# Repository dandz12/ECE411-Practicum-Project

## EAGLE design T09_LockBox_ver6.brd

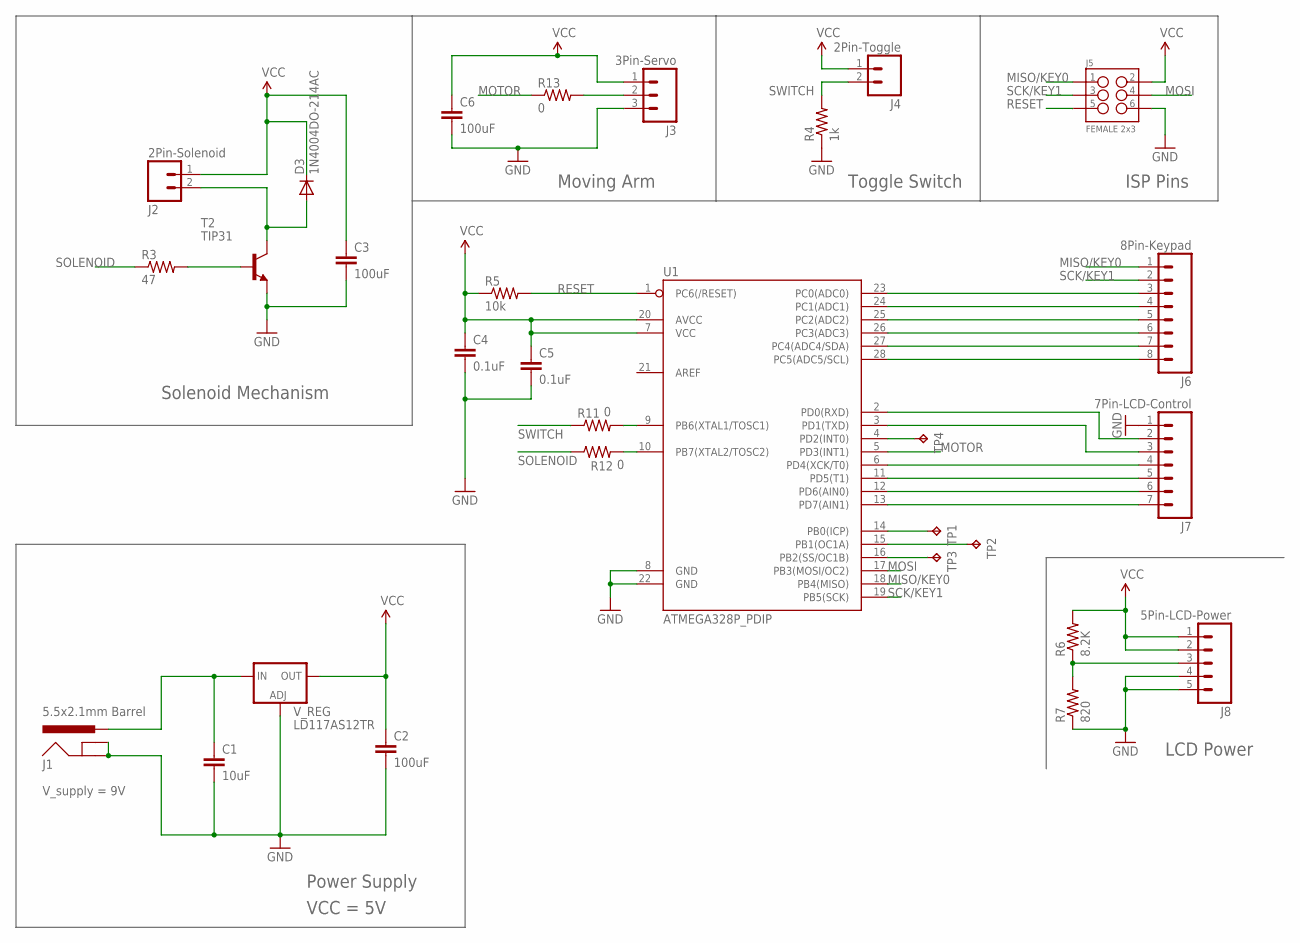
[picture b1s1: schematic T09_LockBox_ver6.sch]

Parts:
C1: 10uF; 0603-CAP
C2, C3, C6: 100uF; 0603-CAP
C4, C5: 0.1uF; 0603-CAP
D3: 1N4004DO-214AC; DO-214AC
J1: 5.5x2.1mm Barrel; POWER_JACK_SMD
J2: 2Pin-Solenoid; 1X02
J3: 3Pin-Servo; 1X03
J4: 2Pin-Toggle; 1X02
J5: FEMALE 2x3; 2X3
J6: 8Pin-Keypad; 1X08_ROUND
J7: 7Pin-LCD-Control; 1X07
J8: 5Pin-LCD-Power; 1X05
R3: 47; 0805
R4: 1k; 0603-RES
R5: 10k; 0603-RES
R6: 8.2K; 0603-RES
R7: 820; 0603-RES
R11, R12, R13: 0; 0603-RES
T2: TIP31; TO220
TP1, TP2, TP3, TP4: TPPAD1-13; P1-13
U1: ATMEGA328P_PDIP; DIL28-3
V_REG: LD117AS12TR; SOT223

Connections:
GND: C1.2, C2.2, C3.2, C4.2, C5.2, C6.2, J1.GND (GNDBREAK), J1.P$4 (GND), J3.3, J5.6, J7.1, J8.4, J8.5, R4.1, R7.1, T2.3 (E), U1.8 (GND), U1.22 (GND), V_REG.1 (ADJ)
MISO/KEY0: J5.1, J6.1, U1.18 (PB4(MISO))
MOSI: J5.4, U1.17 (PB3(MOSI/OC2))
MOTOR: R13.1, U1.5 (PD3(INT1))
unnamed: D3.A, J2.2, T2.2 (C)
unnamed: J8.3, R6.1, R7.2
unnamed: R3.2, T2.1 (B)
unnamed: J7.2, U1.2 (PD0(RXD))
unnamed: R11.2, U1.9 (PB6(XTAL1/TOSC1))
unnamed: R12.2, U1.10 (PB7(XTAL2/TOSC2))
unnamed: J3.2, R13.2
unnamed: J7.3, U1.3 (PD1(TXD))
unnamed: J7.4, U1.6 (PD4(XCK/T0))
unnamed: J7.5, U1.11 (PD5(T1))
unnamed: J7.6, U1.12 (PD6(AIN0))
unnamed: J7.7, U1.13 (PD7(AIN1))
unnamed: J6.3, U1.23 (PC0(ADC0))
unnamed: J6.4, U1.24 (PC1(ADC1))
unnamed: J6.5, U1.25 (PC2(ADC2))
unnamed: J6.6, U1.26 (PC3(ADC3))
unnamed: J6.7, U1.27 (PC4(ADC4/SDA))
unnamed: J6.8, U1.28 (PC5(ADC5/SCL))
unnamed: TP4.TP, U1.4 (PD2(INT0))
unnamed: TP1.TP, U1.14 (PB0(ICP))
unnamed: TP2.TP, U1.15 (PB1(OC1A))
unnamed: TP3.TP, U1.16 (PB2(SS/OC1B))
RESET: J5.5, R5.2, U1.1 (PC6(/RESET))
SCK/KEY1: J5.3, J6.2, U1.19 (PB5(SCK))
SOLENOID: R3.1, R12.1
SWITCH: J4.2, R4.2, R11.1
VCC: C2.1, C3.1, C4.1, C5.1, C6.1, D3.C, J2.1, J3.1, J4.1, J5.2, J8.1, J8.2, R5.1, R6.2, U1.7 (VCC), U1.20 (AVCC), V_REG.4 (OUT)
VIN: C1.1, J1.VIN0 (PWR), V_REG.3 (IN)

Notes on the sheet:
VCC = 5V
Solenoid Mechanism
Moving Arm
ISP Pins
Toggle Switch
Power Supply
LCD Power
V_supply = 9V

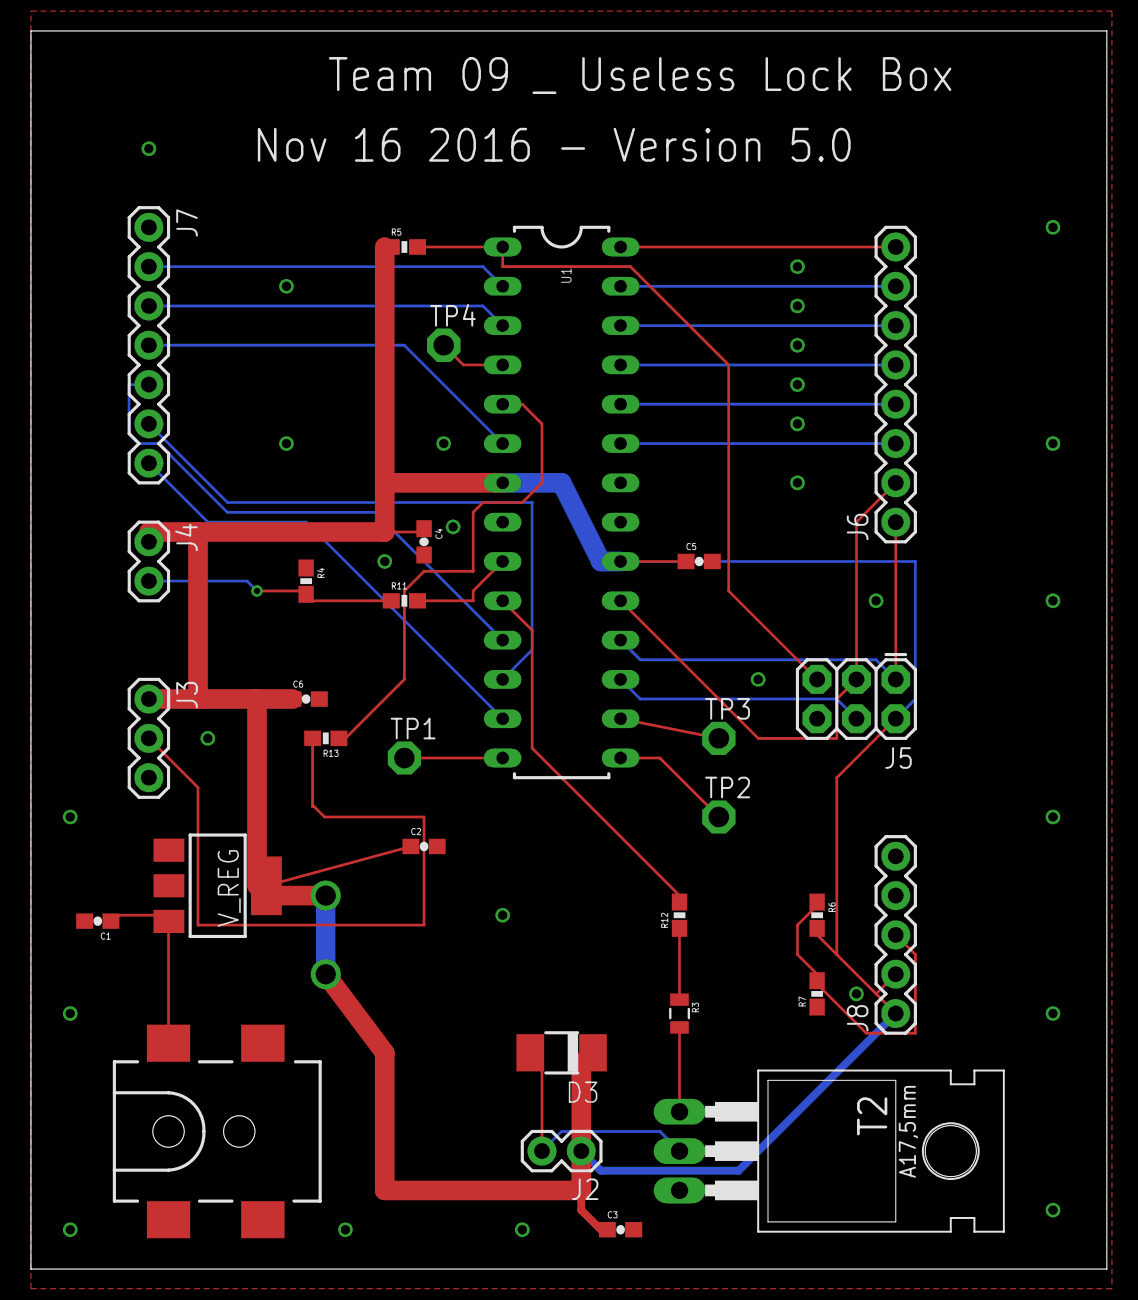
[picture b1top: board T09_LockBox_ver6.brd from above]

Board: 2 copper layers, 69.5 x 80.0 mm, 30 parts (0 on the bottom side), 32 nets.

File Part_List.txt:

Partlist exported from /Users/BumBum/Desktop/T09_LockBox_ver5.0.sch at 11/19/16 9:20 PM

Part  Value            Device           Package        Description			
C1    10uF             CAP0603-CAP      0603-CAP       Capacitor                                                                                                         
C2    100uF            CAP0603-CAP      0603-CAP       Capacitor                                                                                                         
C3    100uF            CAP0603-CAP      0603-CAP       Capacitor                                                                                                         
C4    0.1uF            CAP0603-CAP      0603-CAP       Capacitor                                                                                                         
C5    0.1uF            CAP0603-CAP      0603-CAP       Capacitor                                                                                                         
C6    100uF            CAP0603-CAP      0603-CAP       Capacitor                                                                                                         
D3    1N4004DO-214AC   1N4004DO-214AC   DO-214AC       DIODE                                                                                                             
J1    5.5x2.1mm Barrel POWER_JACKSMD    POWER_JACK_SMD Power Jack                                                 
J2    2Pin-Solenoid    M02PTH           1X02           Header 2                                                                             
J3    3Pin-Servo       M03PTH           1X03           Header 3                                                                                                          
J4    2Pin-Toggle      M02PTH           1X02           Header 2
J5    FEMALE 2x3       M03X2FEMALE      2X3            2x3 .1" header                                             
J6    8Pin-Keypad      M08              1X08_ROUND     Header 8                                                   
J7    7Pin-LCD-Control M07              1X07           Header 7                                                                                                          
J8    5Pin-LCD-Power   M05PTH           1X05           Header 5                                                                                                          
R3    47               RESISTOR0805-RES 0805           Resistor                                                                                                          
R4    1k               RESISTOR0603     0603-RES       Resistor                                                                                                          
R5    10k              RESISTOR0603     0603-RES       Resistor                                                                                                          
R6    8.2K             RESISTOR0603     0603-RES       Resistor                                                                                                          
R7    820              RESISTOR0603     0603-RES       Resistor                                                                                                          
R11   0                RESISTOR0603     0603-RES       Resistor                                                                                                          
R12   0                RESISTOR0603     0603-RES       Resistor                                                                                                          
R13   0                RESISTOR0603     0603-RES       Resistor                                                                                                          
T2    TIP31            TIP31            TO220          NPN Transistor                                                         
TP1   TPPAD1-13        TPPAD1-13        P1-13          Test pad                                                                                                          
TP2   TPPAD1-13        TPPAD1-13        P1-13          Test pad                                                                                                          
TP3   TPPAD1-13        TPPAD1-13        P1-13          Test pad                                                                                                          
TP4   TPPAD1-13        TPPAD1-13        P1-13 in       Test pad                                                                                                          
U1    ATMEGA328P_PDIP  ATMEGA328P_PDIP  DIL28-3        uC used in the Arduino                                                                                            
V_REG LD117AS12TR      LD117AS12TR      SOT223         Positive voltage regulators 1A

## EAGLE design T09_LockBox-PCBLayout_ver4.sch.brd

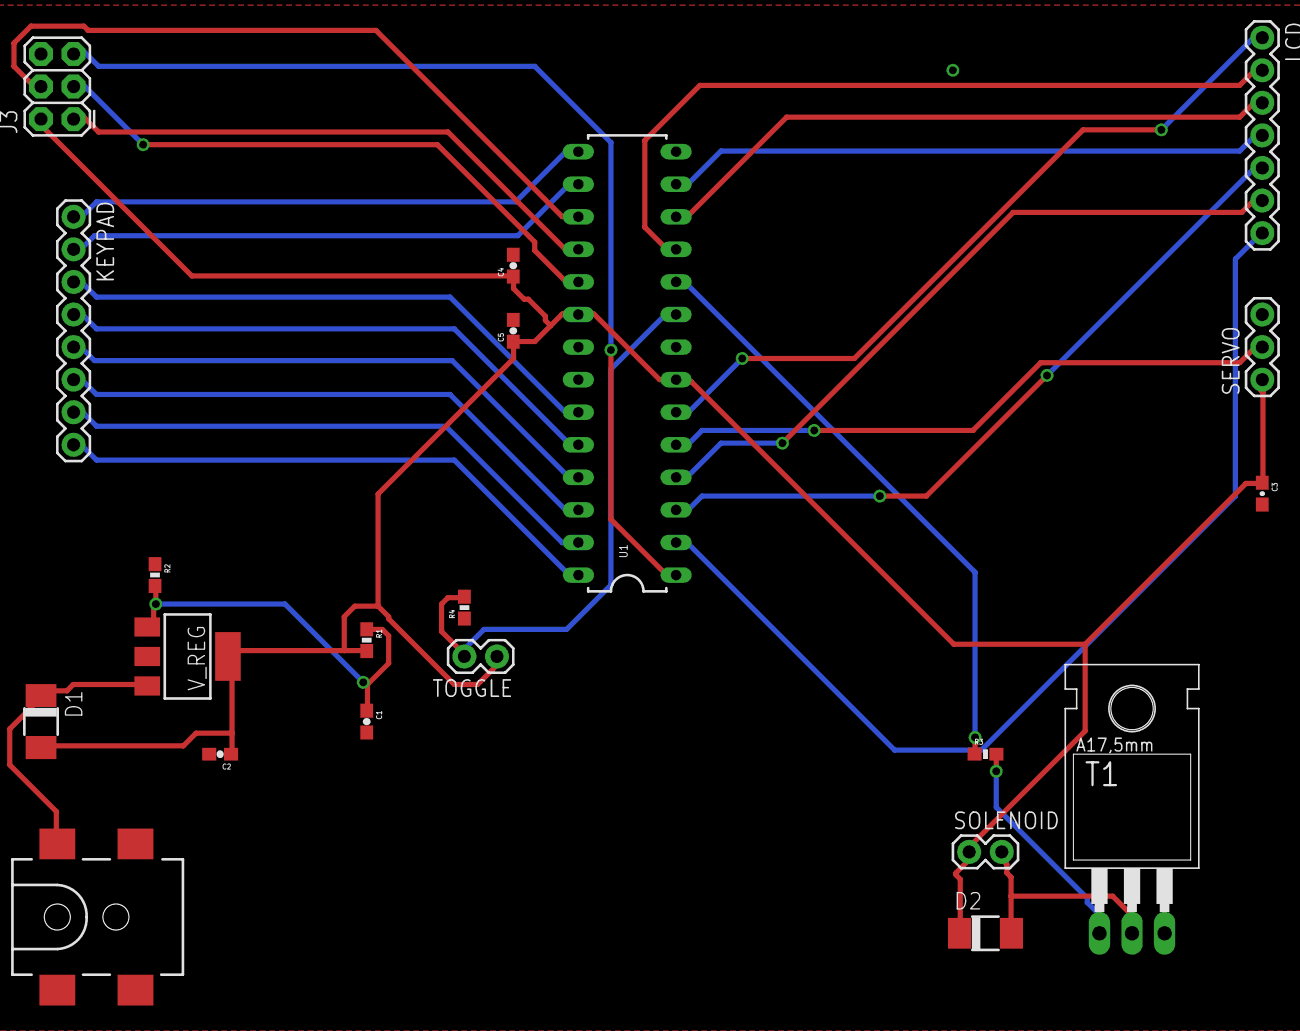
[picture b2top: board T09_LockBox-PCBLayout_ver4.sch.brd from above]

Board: 2 copper layers, 21 parts (0 on the bottom side), 28 nets.

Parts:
C1: 10uF; 0603-CAP
C2, C4, C5: 220uF; 0603-CAP
C3: 470uF; 0603-CAP
D1, D2: 1N4004DO-214AC; DO-214AC
J1: 5.5x2.1mm Barrel; POWER_JACK_SMD
J3: FEMALE 2x3; 2X3
KEYPAD: 8-Pins; 1X08_ROUND
LCD: 7-Pins; 1X07
R1: 120; 0603-RES
R2: 360; 0603-RES
R3: 2k2; 0603-RES
R4: 1k; 0603-RES
SERVO: 3-Pins; 1X03
SOLENOID: 2-Pins; 1X02
T1: TIP31; TO220
TOGGLE: 2-Pins; 1X02
U1: ATMEGA328P_PDIP; DIL28-3
V_REG: LD117AS12TR; SOT223

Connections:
DATA1: LCD.1, U1.6
DATA2: LCD.2, U1.11
DATA3: LCD.3, U1.12
DATA4: LCD.4, U1.13
EN: LCD.7, U1.2
GND: C1.2, C2.2, C3.2, C4.2, C5.2, J1.GND, J1.P$4, J3.6, R2.1, R4.1, SERVO.3, T1.3, U1.8, U1.22
KEY1: KEYPAD.1, U1.15
KEY2: KEYPAD.2, U1.16
KEY3: KEYPAD.3, U1.23
KEY4: KEYPAD.4, U1.24
KEY5: KEYPAD.5, U1.25
KEY6: KEYPAD.6, U1.26
KEY7: KEYPAD.7, U1.27
KEY8: KEYPAD.8, U1.28
MISO: J3.1, U1.18
MOSI: J3.4, U1.17
MOTOR: SERVO.2, U1.5
unnamed: R3.2, T1.1
unnamed: C1.1, R1.1, R2.2, V_REG.1
RESET: J3.5, U1.1
RS: LCD.6, U1.4
SCK: J3.3, U1.19
SOLENOID: R3.1, U1.10
SOLENOID-: D2.A, SOLENOID.2, T1.2
SWITCH: R4.2, TOGGLE.2, U1.9
VCC: C2.1, C3.1, C4.1, C5.1, D1.A, D2.C, J3.2, R1.2, SERVO.1, SOLENOID.1, TOGGLE.1, U1.7, U1.20, V_REG.4
VIN: D1.C, J1.VIN0, V_REG.3
W/R: LCD.5, U1.3

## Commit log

2016-10-08 Add files via upload
    Dwayne added info into the decision matrix
2016-10-08 Add files via upload
    Dwayne's Potential Project Description
2016-10-08 Revert "Revert "Merge pull request #5 from dandz12/Ha's-branch""
    This reverts commit 9b01ece93a4c787b3d0d3d6b80cd6086ba08118c.
2016-10-11 Added rational to matrix
    Requirement #3 asks for a description of the method and rationale for our values, so I just added a paragraph at the bottom.
2016-10-11 Only fix my name :)
2016-10-15 Block diagram for project
2016-10-17 Sample blinking LED code
    I finally got some results in using my Arduino to program the stand-alone ATmega328 with no Arduino bootloader!!! The code below is C code that I just pasted into the Arduino IDE, and it understands 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
    If I set the timer to 100ms, for example, it actually blinks about once every 1.5 seconds. I suspect it has something to do with
    defining the clock speed of the chip, but I am not sure.
2016-10-18 Links we might use
    Hey guys, I thought I'd make a document that has links for common web addresses we might use. Feel free to add more to it.
2016-10-19 ATmega328P data sheet additional info
    There are two data sheets, a short one and a full (444 pages) one. I added the full one and modified the descriptions for each data sheet link.
2016-10-20 Fixing the toggle switch connect to the microprocessor
2016-10-24 LCD writing words sample code
2016-10-25 Adding page number and some more requirements
2016-10-25 feet --> inch mistake fixed
2016-10-31 added link
    for more ATmega tutorials
2016-11-01 Updated with Eagle Libraries
2016-11-01 Voltage regulator datasheet
2016-11-03 Update Useful Links
2016-11-03 LockBox Ver2 No ERC errors
2016-11-03 Added link for student software
    The CAT (Computer Action Team) has a site for free or discounted student software. I downloaded Microsoft Project and I suggest we use it for our project management tool.
2016-11-03 Add files via upload
    Code for the microcontroller to read the keypad and blink an LED.
2016-11-03 Microsoft Project preliminary file for review
    Here is a start to a Project. I added the link for Microsoft downloads from the CAT. Project Professional is free. I added tasks, dates, and people assigned to some tasks. Please feel free to make ad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
2016-11-04 Updated Project
    I added the switch task to the project
2016-11-04 Add files via upload
    This file is still testing the keypad with an LED but is written for our final design.
2016-11-05 Updated Microsoft Project
    I added tasks for the weekly reports, assigned next week's report to me, and added some other stuff like dependancies.
2016-11-05 Updated Microsoft Project
    I added tasks for weekly reports and assigned myself next week's report, added some dependencies, and made other tweeks.
2016-11-06 Final Version of Schematic with block names, bypass caps, ect.
2016-11-06 Final (pending approval by Daniel) Project schedule
    Approved by Thanh, Ha, and Dwayne. The only requirement we didn't follow was to do leveling. We tried to do leveling, but it rearranged a bunch of hard due dates, making the schedule useless.
2016-11-06 Add files via upload
    I added some specifics about who will be designing and manufacturing the box and arm.
2016-11-10 Updated schematic with layout, no DRC errors (read extended description)
    http://docs.oshpark.com/design-tools/eagle/.
    You can ignore DRU errors on the tStop and bStop layers since we automatically prevent silk from being placed on exposed copper.
2016-11-10 Delete T09_LockBox-Schematic_ver4.sch.sch
    Wrong upload
2016-11-10 Delete T09_LockBox-PCBLayout_ver4.sch.brd
    Wrong updload
2016-11-10 Updated schematic with layout, no DRC error (read extended description)
    http://docs.oshpark.com/design-tools/eagle/
    You can ignore DRU errors on the tStop and bStop layers since we automatically prevent silk from being placed on exposed copper.
2016-11-10 Servo Code
    This pastes much more neatly in Atmel Studio, sorry this is kind of a mess and difficult to read.
2016-11-12 Updated servo code
    Sorry it took me so long to get this updated and uploaded.
2016-11-12 Schedule updated
    Updated completeness levels of tasks. No new tasks added.
2016-11-12 Transistor datasheet
2016-11-15 4 bit communication with LCD code with Hello World example
    Example code for printing Hello World in 2 lines
    DDRD=0xFF; // Set port D as output
    lcd_ini(); // initialization of LCD
    LCD_write_string("hello"); // function to print string on LCD
    dis_cmd(0xC0); // move to second line
    LCD_write_string("world"); // function to print string on LCD
2016-11-16 Homework #5
2016-11-17 LockBox-ver5 after Prof.Andrew's Comment
2016-11-17 Layout after Prof.Andrew's comment _ Still need to check again one more time tomorrow before submitting
2016-11-17 Final Version of Schematic and Layout
2016-11-17 Adding some arrangements
2016-11-17 Add files via upload
    Keypad using the new pin assignments
2016-11-18 Update LCD code
    uploaded the older one last time :D
2016-11-19 Update LCD codes (details in extended description)
    Frequency defined = 1MHz
    Clear warning errors while compiling.
2016-11-20 Final fixed-all Schematic
2016-11-20 Final fixed-all Schematic - Uploaded file
2016-11-20 BOM and List of websites to buy
2016-11-22 First full build
    This build has the keypad, screen, servo and solenoid together.
2016-11-24 Updated Test Plan
2016-11-24 Fixed Rev #s
2016-12-02 Change control pins according to the board layout
    Old pin in prototype: RS is D2
    New pin in PCB board: RS is D1
2016-12-03 Update useful link
    with PWM information
2016-12-03 more functions (read extended description)
    isEqual() check if to array is equal
    promtKey() ask for 4-key code
    changePasscode() change passcode sequence
2016-12-03 Update promptKey() function
    the promptKey() function now check if the user enter a 4-numbers code
    implement isNumber(), check if all element of an array is from 0 to 9.
2016-12-07 Added switch
    Todo: clear screen when switch is flipped back
2016-12-07 Finished switch to print
    Almost final, needs some cleaning
2016-12-07 Final Presentation
2016-12-07 outline finish
2016-12-08 Completed Requirement document
2016-12-08 Update full_build.cpp
    Slow the LCD cmd again, due to bug
2016-12-08 Final Presentation update
2016-12-08 Electrical Part List
2016-12-08 Box SOLIDWORK
2016-12-08 No changes made, but I added comments.
2016-12-08 Updated...
2016-12-08 Final update

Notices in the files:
parts and their libraries:
SparkFun-Passives: Licensing: Creative Commons ShareAlike 4.0 International - https://creativecommons.org/licenses/by-sa/4.0
